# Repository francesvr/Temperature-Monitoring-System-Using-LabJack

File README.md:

# Temperature Monitoring System Using LabJack

This PCB has a temperature sensor to monitor the temperature and an LED and buzzer to alert the user when the temperature is below or above the set threshold. The LED is off while the temperature is below the threshold and the buzzer will activate when it is above the threshold. The PWM is set up in the beginning of the code with setting FIO4 as the channel to send the PWM signal to, with divisor as 48MHz/DIV, with divisor of 47, 1 as number of time enabled, and 8-bit timer mode. The program starts off with LED off by DAC0 sending a high signal. Then, the user is asked for the temperature threshold in degrees Celsius. Then, they are asked to choose between two exit strategies; how long they want the program to run for (in seconds) or how many buzzer activations before the program ends. The temperature sensor, which is connected to AIN0, will read the voltage output and multiply it by a 100 to convert to degrees Celsius and continuously compare it with the threshold set by the user to decide whether to activate the LED or the buzzer. If the user chooses to run the program based on the time they provide, and if the temperature is below the threshold, the DAC0 channel which is connected to the LED will send a low signal for the LED to remain on and the program constantly prints the current temperature. If the temperature is above the threshold, the timer value is set to 50% duty cycle to turn the buzzer on and DAC0 will send a high signal to turn the LED off. The program will constantly print that the temperature is high and the current temperature. When the time is done, the program waits for user input to continue terminating the program. In addition, if the user chooses to end the program after a certain amount of buzzer activation, again, the program will constantly print the current temperature and turn the LED on if the temperature is below the threshold. If the temperature is above the threshold, the timer value will be set to 50% duty cycle to turn the buzzer on. The program will stop printing the current temperature and lets the user know how many times the buzzer has been activated, compared to the number of buzzer activations they specified. The buzzer will turn off and the program will continue printing the current temperature again and turns the LED on again. This loop will go on until the number of buzzer activations the user specified has been reached. The user also has the option to exit the program in the beginning of the program if they choose not to continue. Before the program ends, the LED and buzzer turn off and all pins will reset.

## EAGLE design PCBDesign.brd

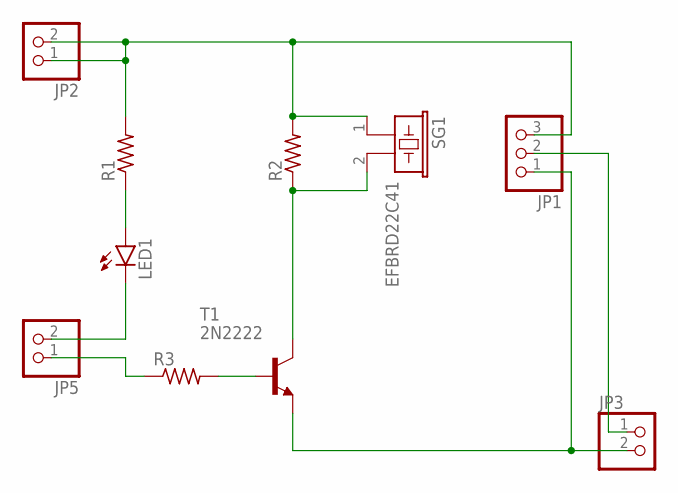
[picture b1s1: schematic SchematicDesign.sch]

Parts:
JP1: PINHD-1X3; 1X03
JP2, JP3, JP5: PINHD-1X2; 1X02
LED1: LED5MM
R1, R2, R3: R-US_0207/10; 0207/10
SG1: EFBRD22C41
T1: 2N2222; TO18

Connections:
unnamed: LED1.A, R1.1
unnamed: JP1.3, JP2.1, JP2.2, R1.2, R2.2, SG1.1
unnamed: JP5.2, LED1.K (C)
unnamed: R3.2, T1.2 (B)
unnamed: R2.1, SG1.2, T1.3 (C)
unnamed: JP5.1, R3.1
unnamed: JP1.1, JP3.2, T1.1 (E)
unnamed: JP1.2, JP3.1

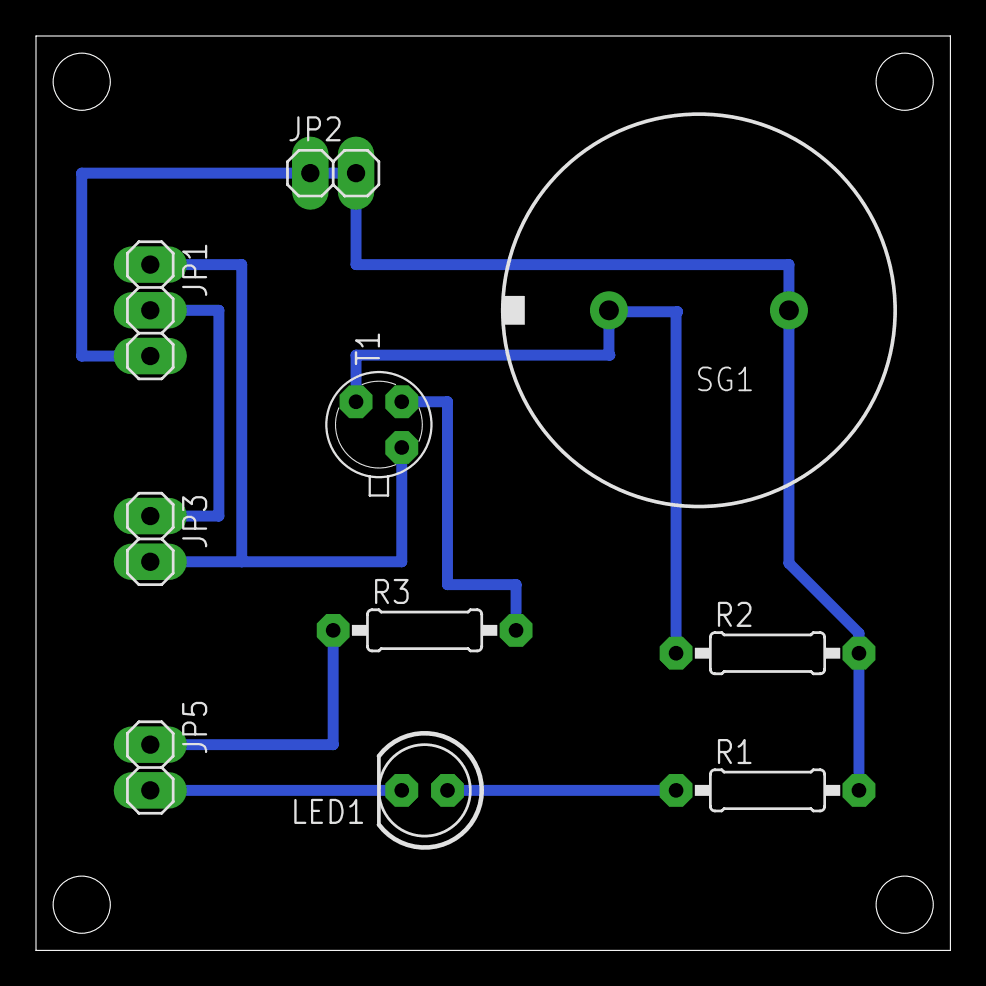
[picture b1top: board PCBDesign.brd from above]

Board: 2 copper layers, 50.8 x 50.8 mm, 10 parts (0 on the bottom side), 8 nets.

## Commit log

2024-12-21 README.md
2024-12-21 TemperatureMonitoringSystem.c
